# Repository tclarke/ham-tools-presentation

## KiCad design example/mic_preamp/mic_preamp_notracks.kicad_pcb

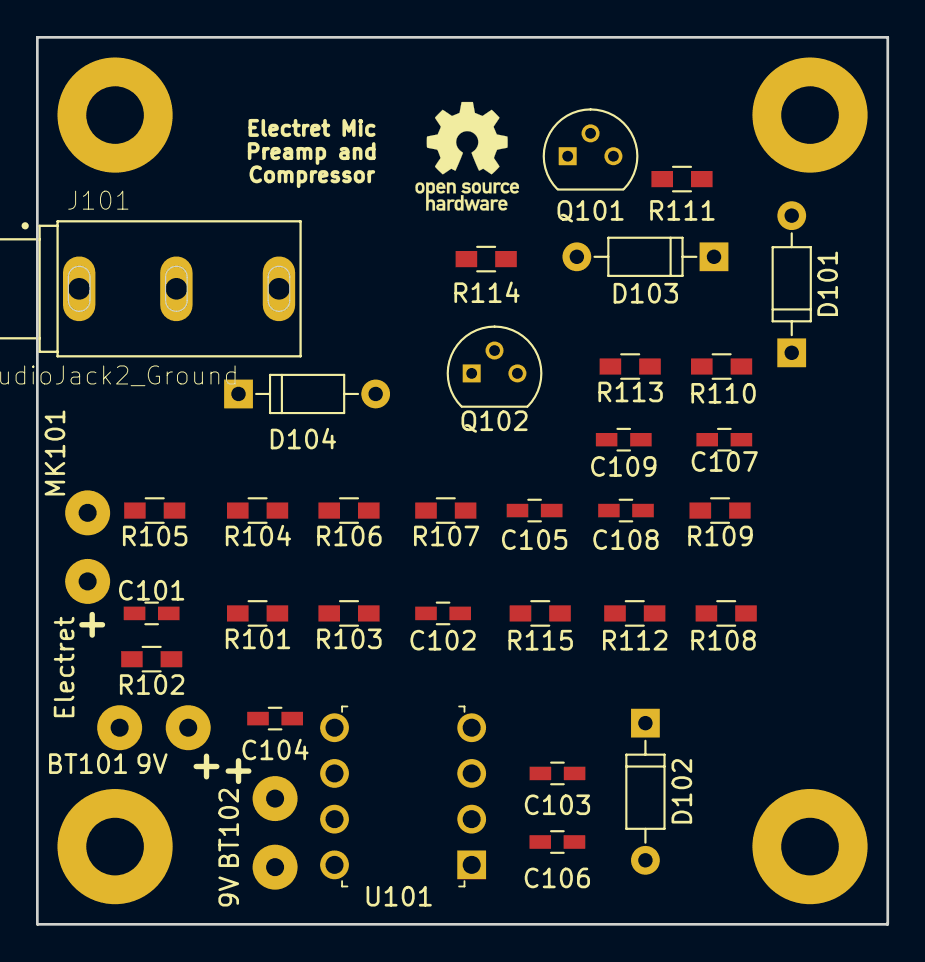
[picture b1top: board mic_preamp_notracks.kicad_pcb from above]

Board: 2 copper layers, 47.2 x 49.3 mm, 40 parts (0 on the bottom side), 22 nets, no tracks yet.

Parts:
BT101, BT102: 9V; SolderWirePad_2x_1mmDrill
C101: 10u; C_0603_HandSoldering
C102, C103, C104: 1n; C_0603_HandSoldering
C105: 100p; C_0603_HandSoldering
C106: 470n; C_0603_HandSoldering
C107, C109: 47n; C_0603_HandSoldering
C108: 1u; C_0603_HandSoldering
D101, D102, D103, D104: 1N4148; D_DO-35_SOD27_P7.62mm_Horizontal
J101: AudioJack2_Ground; CUI_MJ-3502
MK101: Electret; SolderWirePad_2x_1mmDrill
Q101, Q102: 2N2222A; TO-92_Molded_Narrow
R101: 26.1k; R_0603_HandSoldering
R102: 2.2k; R_0603_HandSoldering
R103: 143k; R_0603_HandSoldering
R104: 44.2k; R_0603_HandSoldering
R105: 17.4k; R_0603_HandSoldering
R106: 78.7k; R_0603_HandSoldering
R107: 280k; R_0603_HandSoldering
R108: 6.19k; R_0603_HandSoldering
R109: 48.7k; R_0603_HandSoldering
R110: 10k; R_0603_HandSoldering
R111: 12k; R_0603_HandSoldering
R112: 220k; R_0603_HandSoldering
R113: 750; R_0603_HandSoldering
R114: 5.6k; R_0603_HandSoldering
R115: 100k; R_0603_HandSoldering
REF1, REF2, REF3, REF4: MountingHole_Pad; MountingHole_3.2mm_M3_Pad
REF5: Logo_Open_Hardware_Large; OSHW-Logo_5.7x6mm_SilkScreen
U101: AD8657; DIP-8_W7.62mm

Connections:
Comp_In: C104.1, C106.2, C107.2, R108.1, U101.7
GND: BT101.2, BT102.1, C103.2, C105.1, C108.2, D104.1, J101.1, MK101.1, Q101.1, R105.2, R109.2, R112.2, R115.2, REF1.1, REF2.1, REF3.1, REF4.1
In: C101.2, R101.2
unnamed: C101.1, MK101.2, R102.2
unnamed: C102.1, R104.1, R106.2, U101.1
unnamed: C102.2, R101.1, R103.2
unnamed: C103.1, R103.1, U101.3
unnamed: C104.2, R106.1, R107.2
unnamed: C105.2, R107.1, U101.5
unnamed: C106.1, D101.1, D102.2
unnamed: C107.1, R110.2
unnamed: C108.1, D102.1, Q102.2, R112.1
unnamed: C109.1, J101.2, R115.1
unnamed: C109.2, D103.1, D104.2, R110.1
unnamed: D101.2, Q101.2, Q101.3, R111.2
unnamed: D103.2, R114.2
unnamed: Q102.1, R114.1
unnamed: Q102.3, R113.2
unnamed: R104.2, R105.1, U101.2
unnamed: R108.2, R109.1, U101.6
VCC: BT101.1, R102.1, R111.1, R113.1, U101.4
VEE: BT102.2, U101.8

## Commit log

2019-02-15 Added 'Fork me on github' link
2019-02-15 Fixed indentation issue
2019-02-15 Fixed github overlay
